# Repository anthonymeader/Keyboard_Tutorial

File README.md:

# Keyboard_Tutorial
 Introduction into Designing Keyboard PCB

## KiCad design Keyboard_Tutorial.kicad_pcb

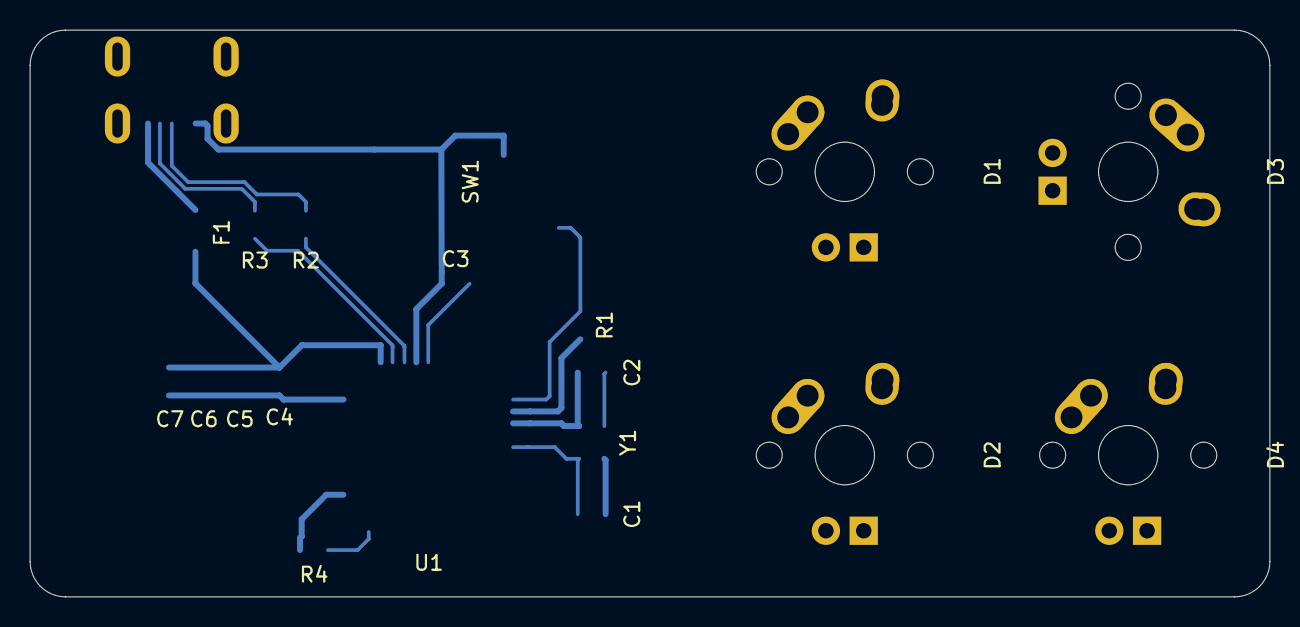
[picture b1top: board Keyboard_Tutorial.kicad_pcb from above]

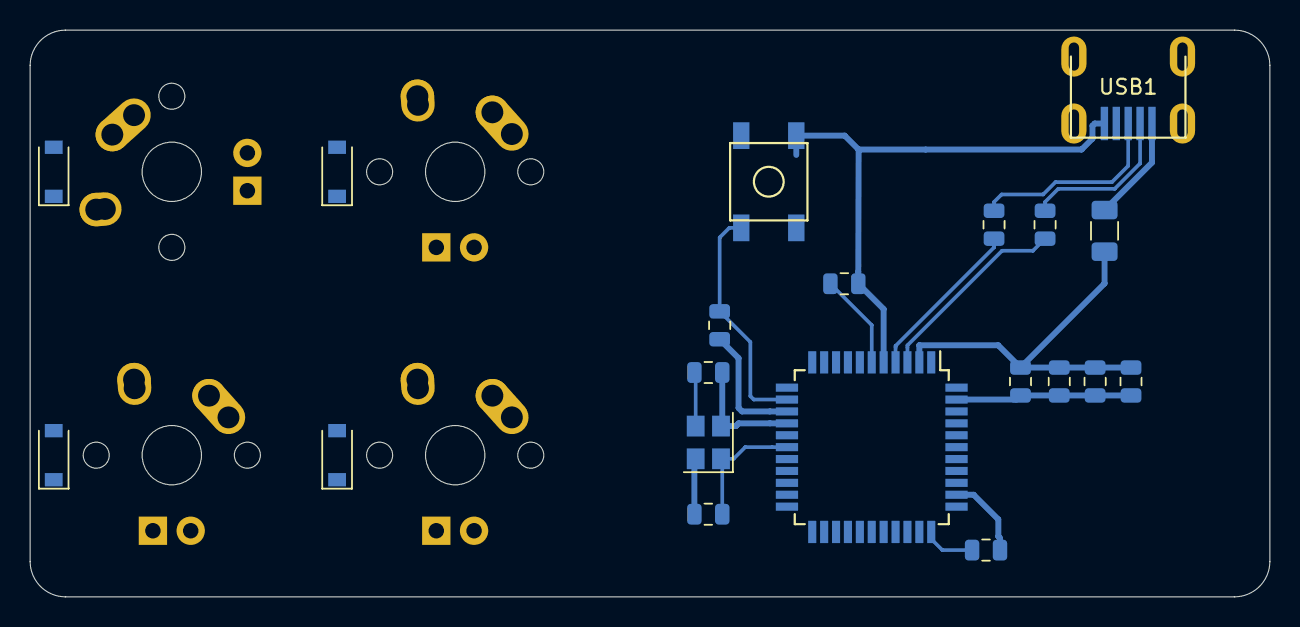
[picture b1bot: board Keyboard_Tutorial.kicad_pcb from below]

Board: 2 copper layers, 83.3 x 38.1 mm, 24 parts (20 on the bottom side), 21 nets.

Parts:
C1, C2, C3, C4, C5, C6, C7: _; C_0805_2012Metric
D1, D2, D3: D_Small; D_SOD-123
D4: _; D_SOD-123
F1: _; Fuse_1206_3216Metric
MX1, MX2, MX3: MX-NoLED; MX-1U
MX4: _; MX-1U
R1, R2, R3, R4: _; R_0805_2012Metric
SW1: _; SKQG-1155865
U1: atmega; TQFP-44_10x10mm_P0.8mm
USB1: Molex-0548190589
Y1: C; Crystal_SMD_3225-4Pin_3.2x2.5mm

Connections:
+5V: C4.1, C5.1, C6.1, C7.2, F1.1, R1.1, U1.2, U1.7, U1.14, U1.34
COL0: MX1.1, MX2.1, U1.29
COL1: MX3.1, MX4.1, U1.28
D+: R2.2, USB1.3
D-: R3.2, USB1.4
GND: C1.1, C2.2, C3.2, C4.2, C5.2, C6.2, C7.1, R4.1, SW1.1, U1.5, U1.15, U1.23, U1.35, U1.43, USB1.1, Y1.2, Y1.4
unnamed: C1.2, U1.17, Y1.1
unnamed: C2.1, U1.16, Y1.3
unnamed: C3.1, U1.6
unnamed: D1.2, MX1.2
unnamed: D2.2, MX2.2
unnamed: D3.2, MX3.2
unnamed: D4.2, MX4.2
unnamed: R1.2, SW1.2, U1.13
unnamed: R2.1, U1.4
unnamed: R3.1, U1.3
unnamed: R4.2, U1.33
unnamed: U1.24, U1.44
ROW0: D1.1, D3.1, U1.27
ROW1: D2.1, D4.1, U1.30
VCC: F1.2, USB1.5

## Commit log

2023-05-30 Initialize Project
2023-05-30 Add submodules
